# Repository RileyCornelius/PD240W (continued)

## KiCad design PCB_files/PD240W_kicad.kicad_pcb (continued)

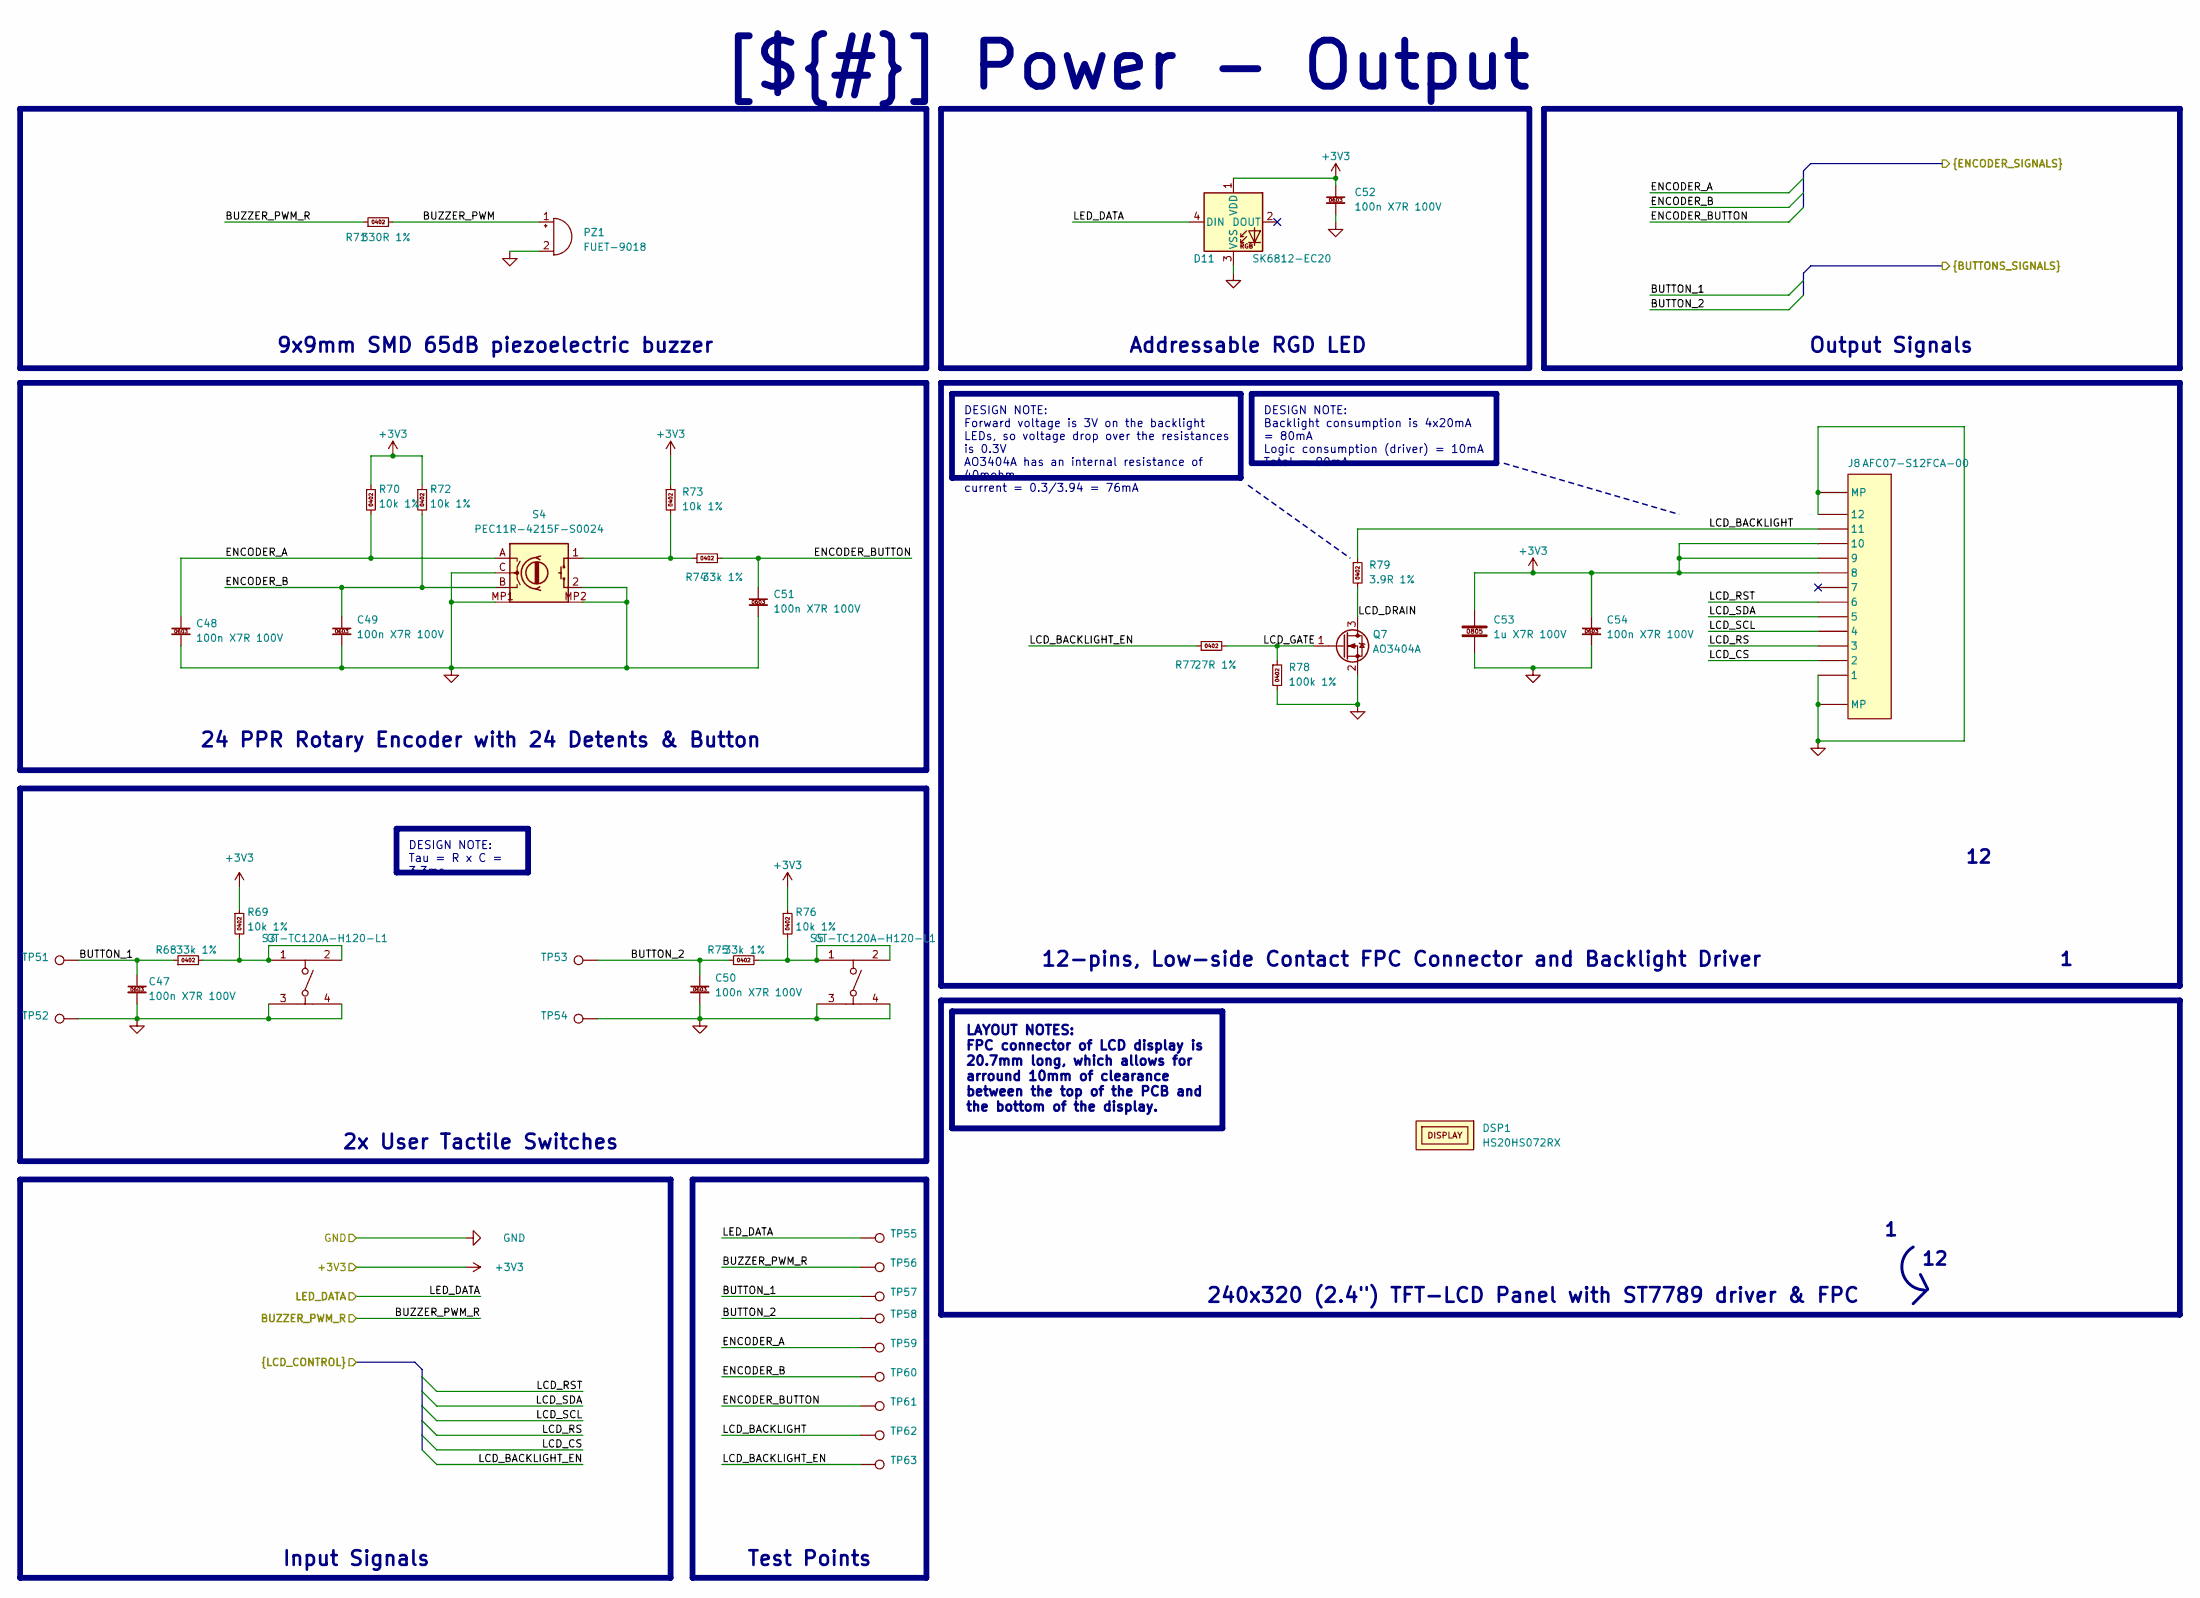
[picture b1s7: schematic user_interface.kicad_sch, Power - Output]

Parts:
C47, C48, C49, C50, C51, C52, C54: 100n X7R 100V; capc_1608_09_l; MFR Part # CL10B104KC8NNNC; LCSC C15725
C53: 1u X7R 100V; capc_2012_14_n; MFR Part # CC0805KKX7R0BB105; LCSC C5370002
D11: SK6812-EC20; MFR Part # SK6812-EC20; LCSC C2909058
DSP1: HS20HS072RX; generic_display_518x362x2_10mm_standoff; MFR Part # HS20HS072RX; LCSC C5329582
J8: AFC07-S12FCA-00; MFR Part # AFC07-S12FCA-00; LCSC C262559
PZ1: FUET-9018; buzzer_9x9x2.1mm; MFR Part # FUET-9018; LCSC C391035
Q7: AO3404A; sot-23-3L_103p_300x130x110_n; MFR Part # AO3404A; LCSC C30010
R68, R74, R75: 33k 1%; resc_1005_04_n; MFR Part # RC0402FR-0733KL; LCSC C138003
R69, R70, R72, R73, R76: 10k 1%; resc_1005_04_n; MFR Part # 0402WGF1002TCE; LCSC C25744
R71: 330R 1%; resc_1005_04_m; MFR Part # 0402WGF3300TCE; LCSC C25104
R77: 27R 1%; resc_1005_04_m; MFR Part # RC0402FR-0727RL; LCSC C138021
R78: 100k 1%; resc_1005_04_m; MFR Part # 0402WGF1003TCE; LCSC C25741
R79: 3.9R 1%; resc_1005_04_m; MFR Part # FRC0402F3R90TS; LCSC C2933095
S3, S5: GT-TC120A-H120-L1; MFR Part # GT-TC120A-H120-L1; LCSC C2762973
S4: PEC11R-4215F-S0024; MFR Part # PEC11R-4215F-S0024; LCSC C143790
TP51, TP52, TP53, TP54: sp_oval_300x100
TP55, TP56, TP57, TP58, TP59, TP60, TP61, TP62, TP63: tp_round_70

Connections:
+3V3: C52.1, C53.1, C54.1, D11.1 (VDD), J8.8, J8.9, J8.10, R69.1, R70.1, R72.1, R73.1, R76.1; also elsewhere on the board
/Project Architecture/MCU - Unit/BUTTON_1: C47.1, R68.1, TP51.1 (1_1), TP57.1 (1_1); also elsewhere on the board
/Project Architecture/MCU - Unit/BUTTON_2: C50.1, R75.1, TP53.1 (1_1), TP58.1 (1_1); also elsewhere on the board
/Project Architecture/MCU - Unit/BUZZER_PWM_R: R71.1, TP56.1 (1_1); also elsewhere on the board
/Project Architecture/MCU - Unit/ENCODER_A: C48.1, R70.2, S4.A, TP59.1 (1_1); also elsewhere on the board
/Project Architecture/MCU - Unit/ENCODER_B: C49.1, R72.2, S4.B, TP60.1 (1_1); also elsewhere on the board
/Project Architecture/MCU - Unit/ENCODER_BUTTON: C51.1, R74.2, TP61.1 (1_1); also elsewhere on the board
/Project Architecture/MCU - Unit/LCD_BACKLIGHT_EN: R77.1, TP63.1 (1_1); also elsewhere on the board
/Project Architecture/MCU - Unit/LCD_CS: J8.2; also elsewhere on the board
/Project Architecture/MCU - Unit/LCD_RS: J8.3; also elsewhere on the board
/Project Architecture/MCU - Unit/LCD_RST: J8.6; also elsewhere on the board
/Project Architecture/MCU - Unit/LCD_SCL: J8.4; also elsewhere on the board
/Project Architecture/MCU - Unit/LCD_SDA: J8.5; also elsewhere on the board
/Project Architecture/MCU - Unit/LED_DATA: D11.4 (DIN), TP55.1 (1_1); also elsewhere on the board
/Project Architecture/User - Interface/BUZZER_PWM: PZ1.1 (+), R71.2
/Project Architecture/User - Interface/LCD_BACKLIGHT: J8.11, R79.1, TP62.1 (1_1)
/Project Architecture/User - Interface/LCD_DRAIN: Q7.3 (D), R79.2
/Project Architecture/User - Interface/LCD_GATE: Q7.1 (G), R77.2, R78.1
GND: C47.2, C48.2, C49.2, C50.2, C51.2, C52.2, C53.2, C54.2, D11.3 (VSS), J8.1, J8.12, J8.MP1 (MP), J8.MP2 (MP), PZ1.2 (-), Q7.2 (S), R78.2, S3.3, S3.4, S4.2, S4.C, S4.MP1, S4.MP2, S5.3, S5.4, TP52.1 (1_1), TP54.1 (1_1); also elsewhere on the board
unnamed: R68.2, R69.2, S3.1, S3.2
unnamed: R73.2, R74.1, S4.1
unnamed: R75.2, R76.2, S5.1, S5.2

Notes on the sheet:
9x9mm SMD 65dB piezoelectric buzzer
Addressable RGD LED
12-pins, Low-side Contact FPC Connector and Backlight Driver
240x320 (2.4") TFT-LCD Panel with ST7789 driver & FPC
24 PPR Rotary Encoder with 24 Detents & Button
Input Signals
Test Points
Output Signals
2x User Tactile Switches
DESIGN NOTE: Backlight consumption is 4x20mA = 80mA Logic consumption (driver) = 10mA Total = 90mA
DESIGN NOTE: Tau = R x C = 3.3ms
DESIGN NOTE: Forward voltage is 3V on the backlight LEDs, so voltage drop over the resistances is 0.3V AO3404A has an internal resistance of 40mohm. current = 0.3/3.94 = 76mA
LAYOUT NOTES: FPC connector of LCD display is 20.7mm long, which allows for arround 10mm of clearance between the top of the PCB and the bottom of the display.
[${#}] ${TITLE}

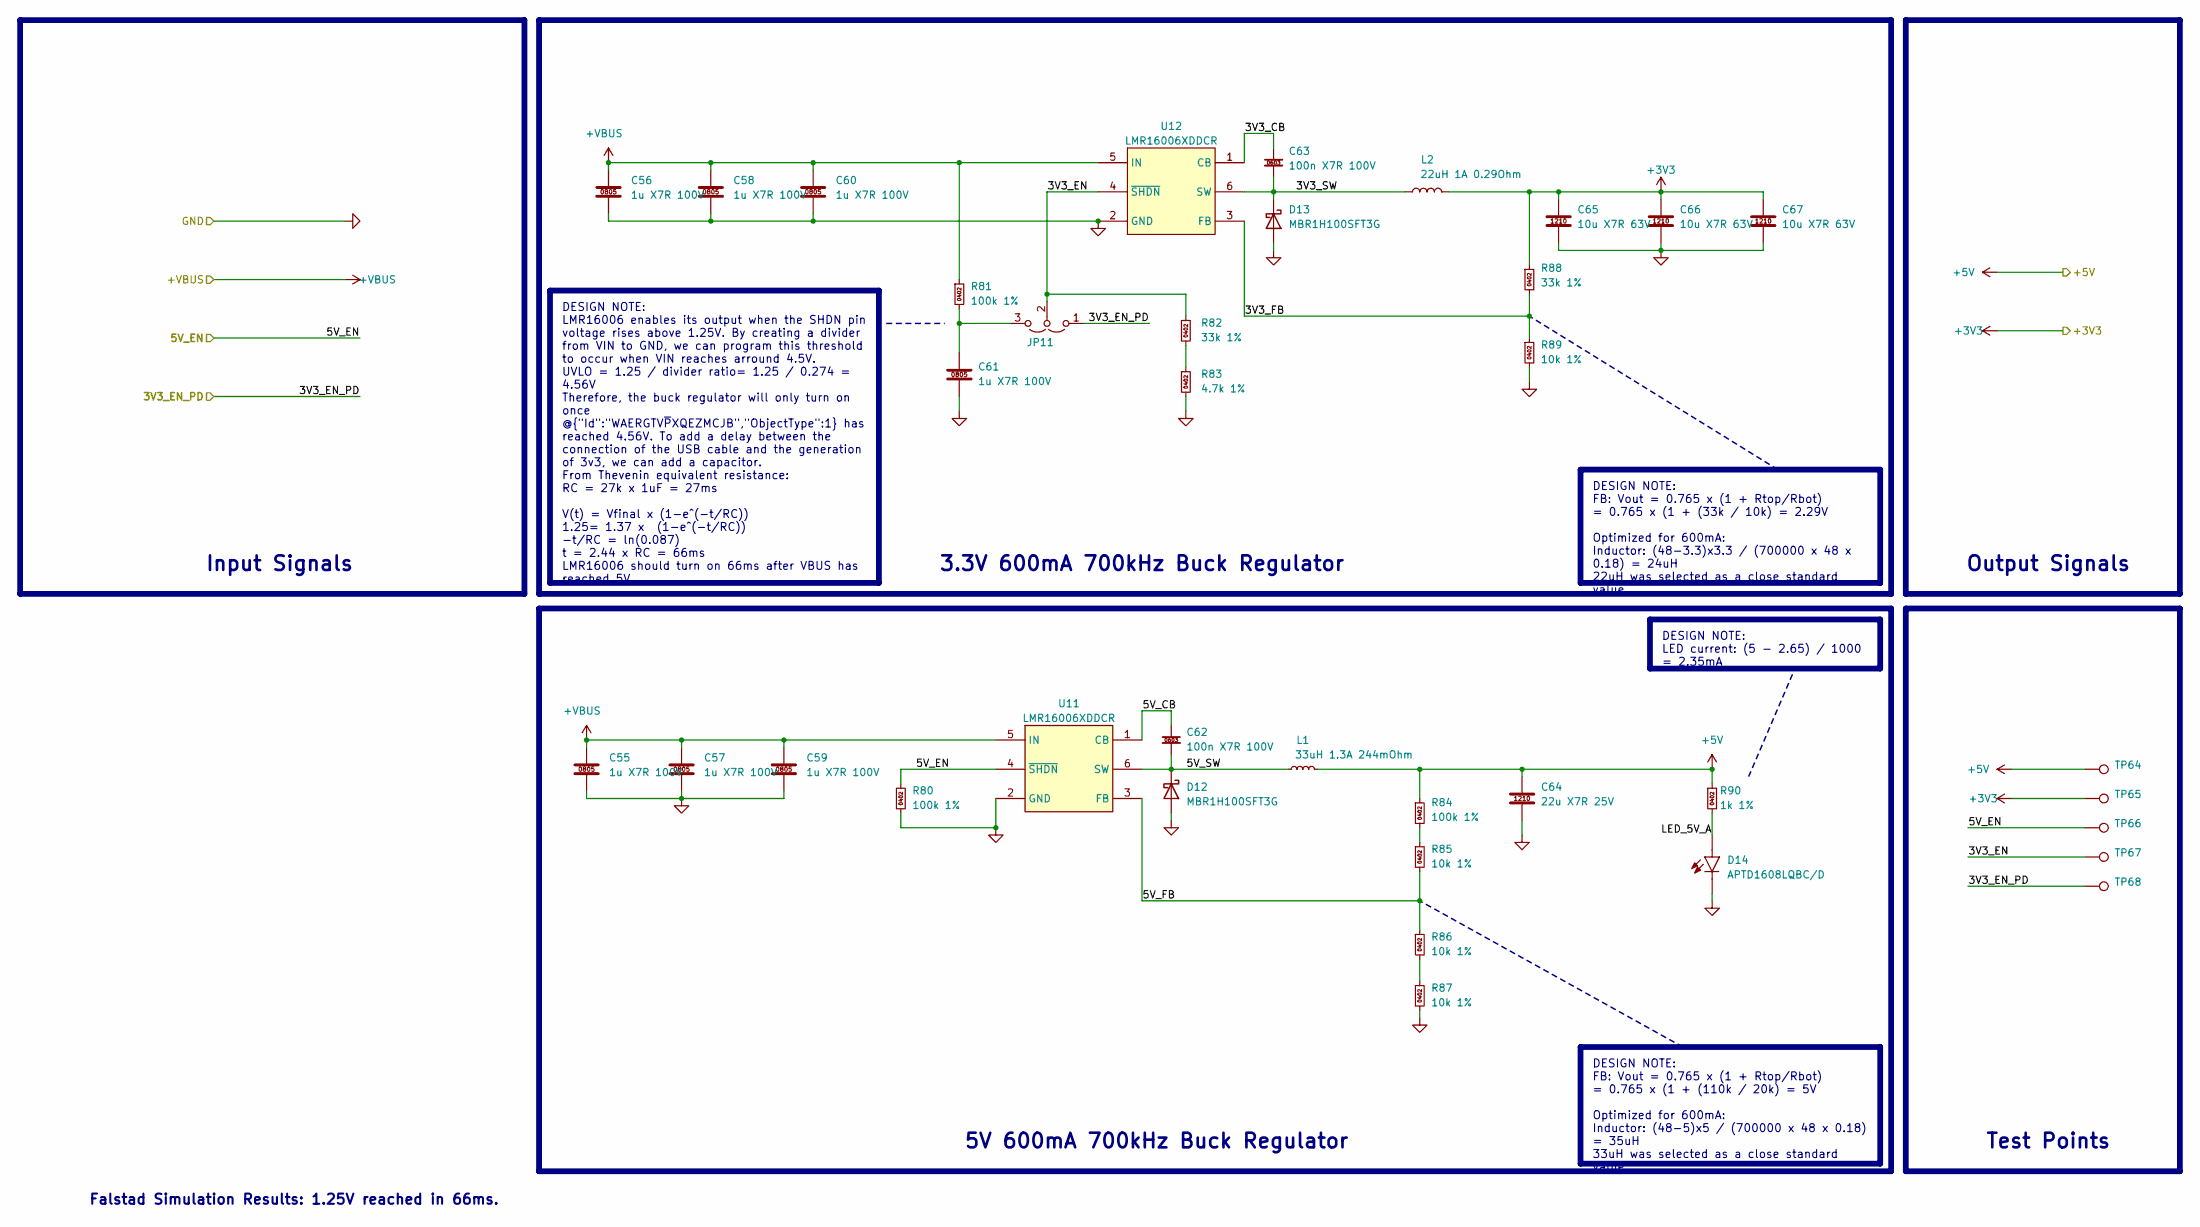
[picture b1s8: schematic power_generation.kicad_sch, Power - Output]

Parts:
C55, C56, C57, C58, C59, C60, C61: 1u X7R 100V; capc_2012_14_n; MFR Part # CC0805KKX7R0BB105; LCSC C5370002
C62, C63: 100n X7R 100V; capc_1608_09_l; MFR Part # CL10B104KC8NNNC; LCSC C15725
C64: 22u X7R 25V; capc_3225_27_n; MFR Part # CL32B226KAJNNNE; LCSC C309062
C65, C66, C67: 10u X7R 63V; capc_3225_27_n; MFR Part # GRM32ER71J106KA12L; LCSC C437568
D12, D13: MBR1H100SFT3G; sod-123fl_305p_260x160x90_n; MFR Part # MBR1H100SFT3G; LCSC C235757
D14: APTD1608LQBC/D; kingbright_0603_blue; MFR Part # APTD1608LQBC/D; LCSC C5344742
JP11: jumper_solder_3pad_no; jumper_solder_3pad_no_40x40_20
L1: 33uH 1.3A 244mOhm; L_APV_ANR5020; MFR Part # SMNR5040-330MT; LCSC C9390
L2: 22uH 1A 0.29Ohm; SWPA4030S220MT; MFR Part # SWPA4030S220MT; LCSC C83472
R80, R81, R84: 100k 1%; resc_1005_04_m; MFR Part # 0402WGF1003TCE; LCSC C25741
R82, R88: 33k 1%; resc_1005_04_n; MFR Part # RC0402FR-0733KL; LCSC C138003
R83: 4.7k 1%; resc_1005_04_m; MFR Part # 0402WGF4701TCE; LCSC C25900
R85, R86, R87, R89: 10k 1%; resc_1005_04_n; MFR Part # 0402WGF1002TCE; LCSC C25744
R90: 1k 1%; resc_1005_04_m; MFR Part # 0402WGF1001TCE; LCSC C11702
TP64, TP65, TP66, TP67, TP68: tp_round_70
U11, U12: LMR16006XDDCR; sot6_p95_290x180x110_n; MFR Part # LMR16006XDDCR; LCSC C87080

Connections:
+3V3: C65.1, C66.1, C67.1, L2.2, R88.1, TP65.1 (1_1); also elsewhere on the board
+5V: C64.1, L1.2, R84.1, R90.1, TP64.1 (1_1); also elsewhere on the board
+VBUS: C55.1, C56.1, C57.1, C58.1, C59.1, C60.1, R81.1, U11.5 (IN), U12.5 (IN); also elsewhere on the board
/Project Architecture/MCU - Unit/5V_EN: R80.1, TP66.1 (1_1), U11.4 (~SHDN); also elsewhere on the board
/Project Architecture/Power - Generation/3V3_CB: C63.1, U12.1 (CB)
/Project Architecture/Power - Generation/3V3_EN: JP11.2 (C), R82.1, TP67.1 (1_1), U12.4 (~SHDN)
/Project Architecture/Power - Generation/3V3_EN_PD: JP11.1 (A), TP68.1 (1_1); also elsewhere on the board
/Project Architecture/Power - Generation/3V3_FB: R88.2, R89.1, U12.3 (FB)
/Project Architecture/Power - Generation/3V3_SW: C63.2, D13.1 (K), L2.1, U12.6 (SW)
/Project Architecture/Power - Generation/5V_CB: C62.1, U11.1 (CB)
/Project Architecture/Power - Generation/5V_FB: R85.2, R86.1, U11.3 (FB)
/Project Architecture/Power - Generation/5V_SW: C62.2, D12.1 (K), L1.1, U11.6 (SW)
/Project Architecture/Power - Generation/LED_5V_A: D14.2 (A), R90.2
GND: C55.2, C56.2, C57.2, C58.2, C59.2, C60.2, C61.2, C64.2, C65.2, C66.2, C67.2, D12.2 (A), D13.2 (A), D14.1 (C), R80.2, R83.2, R87.2, R89.2, U11.2 (GND), U12.2 (GND); also elsewhere on the board
unnamed: C61.1, JP11.3 (B), R81.2
unnamed: R82.2, R83.1
unnamed: R84.2, R85.1
unnamed: R86.2, R87.1

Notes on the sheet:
Input Signals
Output Signals
Test Points
3.3V 600mA 700kHz Buck Regulator
Falstad Simulation Results: 1.25V reached in 66ms.
5V 600mA 700kHz Buck Regulator
DESIGN NOTE: LMR16006 enables its output when the SHDN pin voltage rises above 1.25V. By creating a divider from VIN to GND, we can program this threshold to occur when VIN reaches arround 4.5V. UVLO = 1.25 / divider ratio= 1.25 / 0.274 = 4.56V Therefore, the buck regulator will only turn on once @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
DESIGN NOTE: FB: Vout = 0.765 x (1 + Rtop/Rbot) = 0.765 x (1 + (33k / 10k) = 2.29V Optimized for 600mA: Inductor: (48-3.3)x3.3 / (700000 x 48 x 0.18) = 24uH 22uH was selected as a close standard value.
DESIGN NOTE: LED current: (5 - 2.65) / 1000 = 2.35mA
DESIGN NOTE: FB: Vout = 0.765 x (1 + Rtop/Rbot) = 0.765 x (1 + (110k / 20k) = 5V Optimized for 600mA: Inductor: (48-5)x5 / (700000 x 48 x 0.18) = 35uH 33uH was selected as a close standard value.

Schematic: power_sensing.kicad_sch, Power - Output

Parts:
C23, C24, C25, C26, C27: 100n X7R 100V; capc_1608_09_l; MFR Part # CL10B104KC8NNNC; LCSC C15725
NT1: nt_2pad_20x20_20_60x20; NetTie-2_SMD_Pad0.5mm
R22, R23, R25: 100k 1%; resc_1005_04_m; MFR Part # 0402WGF1003TCE; LCSC C25741
R24: 10k 1%; resc_1005_04_n; MFR Part # 0402WGF1002TCE; LCSC C25744
R26, R32: 4.7k 1%; resc_1005_04_m; MFR Part # 0402WGF4701TCE; LCSC C25900
R27: 10k @25°C; resc_1005_04_m; MFR Part # SDNT1005X103F3950FTF; LCSC C95939
R28, R30, R31: 27R 1%; resc_1005_04_m; MFR Part # RC0402FR-0727RL; LCSC C138021
R29: 8m 1%; WSLP1206_n_current_sense_6m_to_50m; MFR Part # HoLLR1206-1W-8mR-1%; LCSC C2988654
TP27, TP28, TP29, TP30: tp_round_70
U7: INA228AIDGSR; vssop10_50p_300x300x110_mfg; MFR Part # INA228AIDGSR; LCSC C2887910
U8: SN74LVC1G17DBVR; sot25_95p_300x280x145_jedec_mo-178-aa_n; MFR Part # SN74LVC1G17DBVR; LCSC C7836

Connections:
+3V3: C26.1, C27.1, R26.1, U7.6 (VS), U8.5 (VCC); also elsewhere on the board
+VBUS: R22.1, R25.1; also elsewhere on the board
+VBUS_OUT: R29.2, R30.1, TP30.1 (1_1), U7.8 (VBUS); also elsewhere on the board
+VBUS_SENSED: R28.1, R29.1; also elsewhere on the board
/Project Architecture/MCU - Unit/I2C0_SCL: U7.5 (SCL); also elsewhere on the board
/Project Architecture/MCU - Unit/I2C0_SDA: U7.4 (SDA); also elsewhere on the board
/Project Architecture/MCU - Unit/SW_EN_READ: R32.2, TP29.1 (1_1); also elsewhere on the board
/Project Architecture/MCU - Unit/TEMP_SENSE: C24.1, R26.2, R27.1; also elsewhere on the board
/Project Architecture/MCU - Unit/V_SENSE: C23.1, R23.2, R24.1, TP27.1 (1_1); also elsewhere on the board
/Project Architecture/Power - PD Controller/SWITCH_EN: R31.2, TP28.1 (1_1), U8.2 (A); also elsewhere on the board
/Project Architecture/Power - Sensing/INA_ALERT: R31.1, U7.3 (ALERT)
/Project Architecture/Power - Sensing/SENSE_N: C25.2, R30.2, U7.9 (IN-)
/Project Architecture/Power - Sensing/SENSE_P: C25.1, R28.2, U7.10 (IN+)
GND: C23.2, C24.2, C26.2, C27.2, NT1.2, R24.2, U7.1 (A1), U7.2 (A0), U7.7 (GND), U8.3 (GND); also elsewhere on the board
unnamed: NT1.1, R27.2
unnamed: R22.2, R23.1, R25.2
unnamed: R32.1, U8.4 (Y)

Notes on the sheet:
Test Points
Input Signals
85-V, 20-Bit, Ultra-Precise Power/Energy/Charge Monitor With I²C Interface
Temperature Sensing
Output Signals
Input Voltage Sensing
DESIGN NOTE: B-Constant is 3950K 1.2k @ 80°C -> 0.67V 2.5k @ 60°C -> 1.14V 10k @ 25°C -> 2.24V 13k @ 20°C -> 2.42V
DESIGN NOTE: I2C pullups are on Power - PD Conroller schematic
DEBUG NOTE: INA228AIDGSR address when A1 & A0 are tied to GND is 0x40 (7 bits 1000000) (see page 19)
DESIGN NOTE: ADCRANGE = 1 (+- 40.96 mV range) V_{SENSE} = 5A x 0.008 = 40 mV. This utilizes 97.6% of the ADC range, providing the highest possible resolution. Power Dissipation: P = 5² x 0.008 = 0.2W
LAYOUT NOTES: NTC must be placed close and thermally coupled to the ground plane near the relevant heat source. Route away from noisy traces.
LAYOUT NOTES: Place capacitor close to MCU DC pin. Route away from noisy traces.
[${#}] ${TITLE}
DEBUG NOTE: Low side measurement is used to improve thermal coupling, which invert the maths in software.
DESIGN NOTE: Network ratio = 1/16 = 0.0625 @48V V_SENSE = 3V @5V V_SENSE = 0.31V
DEBUG NOTE: ALERT is open-drain and can be configured to latch or not latch the overcurrent event.
DESIGN NOTE: SN74LVC1G17 is a safety buffer to prevent software mistakes. Driving SWEN_READ cannot activate the power switch.

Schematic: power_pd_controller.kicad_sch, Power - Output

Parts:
C9, C12, C14, C15: 10u X7R 63V; capc_3225_27_n; MFR Part # GRM32ER71J106KA12L; LCSC C437568
C10, C16, C20, C21: 100n X7R 100V; capc_1608_09_l; MFR Part # CL10B104KC8NNNC; LCSC C15725
C11, C13: 220p X7R 50V; capc_1005_06_l; MFR Part # CL05B221KB5NNNC; LCSC C296710
C17, C18, C19: 3.3u X5R 25V; capc_1608_09_n; MFR Part # TCC0603X5R335M250CT; LCSC C5360803
C22: 2.2u X7R 100V; capc_2012_14_m; MFR Part # HHV0805R7225K101NSLJ; LCSC C22367838
D5: D3V3F4U6S-7; sot363_sc88_65p_200x125x110_n; MFR Part # D3V3F4U6S-7; LCSC C1869321
D6: B0520LW-7-F; sod-123_270x155135_n; MFR Part # B0520LW-7-F; LCSC C155367
D7: APTD1608LQBC/D; kingbright_0603_blue; MFR Part # APTD1608LQBC/D; LCSC C5344742
J2: 61300411121; we_61300411121; MFR Part # 61300411121; LCSC C5184785; not fitted
JP3, JP4, JP5, JP6, JP7, JP8: jumper_solder_2pad_no; jumper_solder_2pad_no_40x40_20
JP9: jumper_solder_2pad_no_kicad; SolderJumper-2_P1.3mm_Open_RoundedPad1.0x1.5mm
JP10: jumper_solder_3pad_12nc_kicad; SolderJumper-3_P1.3mm_Bridged2Bar12_RoundedPad1.0x1.5mm
Q3, Q4, Q6: AO3404A; sot-23-3L_103p_300x130x110_n; MFR Part # AO3404A; LCSC C30010
Q5: SQJB90EP-T1_GE3; PowerPAKSO-8_127p_513x615x120_n; MFR Part # SQJB90EP-T1_GE3; LCSC C727731
R7, R8, R10, R11, R17: 4.7k 1%; resc_1005_04_m; MFR Part # 0402WGF4701TCE; LCSC C25900
R9, R12, R16: 10k 1%; resc_1005_04_n; MFR Part # 0402WGF1002TCE; LCSC C25744
R13, R14, R15, R19, R20: 100k 1%; resc_1005_04_m; MFR Part # 0402WGF1003TCE; LCSC C25741
R18: 27R 1%; resc_1005_04_m; MFR Part # RC0402FR-0727RL; LCSC C138021
R21: 330R 1%; resc_1005_04_m; MFR Part # 0402WGF3300TCE; LCSC C25104
TP14, TP15, TP16, TP17, TP18, TP19, TP20, TP21, TP22, TP23, TP24, TP25, TP26: tp_round_70
U2: TPS26750SRSMR; qfn32_40p_400x400x100_tp_280x280_mfg; MFR Part # TPS26750SRSMR; LCSC C42166327
U3: CAT24C512YI-GT3; JEDEC_MO-153_AA; MFR Part # CAT24C512YI-GT3; LCSC C56096
U4: LM2765; sot236_p95_290x160x110_n; MFR Part # LM2765M6X/NOPB; LCSC C140270
U5: 74LVC1G08SE-7; sot353_65p_200x125x110_mo-203-aa_n; MFR Part # 74LVC1G08SE-7; LCSC C460522
U6: LTC7004x; msop_10p_300x490x110_tp168x188_n; MFR Part # LTC7004EMSE#PBF; LCSC C690105

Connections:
+1V5_LDO: C9.1, TP23.1 (1_1), U2.2 (ADCIN1), U2.3 (ADCIN2), U2.4 (LDO_1V5)
+3V3: C14.1, D5.5, D7.2 (A), U2.32 (VIN_3V3); also elsewhere on the board
+3V3_EEPROM: C16.1, J2.1, JP9.1 (A), U3.8 (VCC)
+3V3_LDO: C12.1, C17.1, C21.1, D6.2 (A), JP9.2 (B), R7.1, R8.1, R9.1, R10.1, R11.1, R12.1, R14.1, R15.1, TP24.1 (1_1), U2.1 (LDO_3V3), U4.1 (IN), U5.5 (VCC); also elsewhere on the board
+6V6_LDO: C19.1, D6.1 (K), TP25.1 (1_1), U4.5 (OUT), U6.1 (VCC)
+VBUS: JP10.3 (B), Q5.5 (D); also elsewhere on the board
+VBUS_LV: C10.1, U2.26 (VBUS), U2.27 (VBUS); also elsewhere on the board
+VBUS_SENSED: Q5.6 (D), TP22.1 (1_1); also elsewhere on the board
/Project Architecture/MCU - Unit/GPIO14_R: JP8.2 (B); also elsewhere on the board
/Project Architecture/MCU - Unit/GPIO15_R: JP7.2 (B); also elsewhere on the board
/Project Architecture/MCU - Unit/I2C0_SCL: R8.2, U2.9 (I2CT_SCL); also elsewhere on the board
/Project Architecture/MCU - Unit/I2C0_SDA: R7.2, U2.8 (I2CT_SDA); also elsewhere on the board
/Project Architecture/MCU - Unit/PD_GPIO1: TP20.1 (1_1), U2.6 (GPIO1); also elsewhere on the board
/Project Architecture/MCU - Unit/PD_GPIO3: TP21.1 (1_1), U2.18 (GPIO3); also elsewhere on the board
/Project Architecture/MCU - Unit/SWITCH_EN_MANUAL: R13.1, U5.2 (B); also elsewhere on the board
/Project Architecture/MCU - Unit/USB_PD_IRQ: R9.2, TP26.1 (1_1), U2.10 (*I2CT_IRQ); also elsewhere on the board
/Project Architecture/Power - Generation/3V3_EN_PD: U2.31 (GPIO6); also elsewhere on the board
/Project Architecture/Power - PD Controller/CAP+: C18.1, U4.6 (CAP+)
/Project Architecture/Power - PD Controller/CAP-: C18.2, U4.3 (CAP-)
/Project Architecture/Power - PD Controller/CC1: C13.1, U2.24 (CC1); also elsewhere on the board
/Project Architecture/Power - PD Controller/CC2: C11.1, U2.25 (CC2); also elsewhere on the board
/Project Architecture/Power - PD Controller/EPR_EN: U2.7 (GPIO2); also elsewhere on the board
/Project Architecture/Power - PD Controller/I2CC_IRQ: R12.2, U2.17 (*I2CC_IRQ)
/Project Architecture/Power - PD Controller/I2CC_SCL: JP6.2 (B), U2.16 (I2CC_SCL)
/Project Architecture/Power - PD Controller/I2CC_SCL_EEPROM: JP4.2 (B), JP6.1 (A), JP7.1 (A), R11.2, U3.6 (SCL)
/Project Architecture/Power - PD Controller/I2CC_SCL_EXT: D5.1, J2.2, JP4.1 (A)
/Project Architecture/Power - PD Controller/I2CC_SDA: JP5.2 (B), U2.15 (I2CC_SDA)
/Project Architecture/Power - PD Controller/I2CC_SDA_EEPROM: JP3.2 (B), JP5.1 (A), JP8.1 (A), R10.2, U3.5 (SDA)
/Project Architecture/Power - PD Controller/I2CC_SDA_EXT: D5.6, J2.3, JP3.1 (A)
/Project Architecture/Power - PD Controller/LTC_BST: C22.2, U6.9 (BST)
/Project Architecture/Power - PD Controller/LTC_GATE: Q5.2 (G), Q5.4 (G), R18.2, R19.2, R20.2, TP19.1 (1_1), U6.6 (TGDN)
/Project Architecture/Power - PD Controller/POWER_PATH_EN: Q3.1 (G), TP14.1 (1_1), U2.20 (POWER_PATH_EN)
/Project Architecture/Power - PD Controller/PP5V: C15.1, U2.28 (PP5V), U2.29 (PP5V)
/Project Architecture/Power - PD Controller/PP_EN1: Q3.3 (D), Q4.1 (G), R14.2, TP15.1 (1_1)
/Project Architecture/Power - PD Controller/PP_EN2: Q4.3 (D), R15.2, TP16.1 (1_1), U5.1 (A)
/Project Architecture/Power - PD Controller/PP_EN3: R16.1, R17.1, TP17.1 (1_1), U5.4 (Y)
/Project Architecture/Power - PD Controller/SWITCH_EN: Q6.1 (G), R17.2, U6.4 (INP); also elsewhere on the board
/Project Architecture/Power - PD Controller/TS: C22.1, JP10.1 (A), JP10.2 (C), Q5.1 (S), Q5.3 (S), TP18.1 (1_1), U6.8 (TS)
/Project Architecture/Power - PD Controller/~FLT: U2.5 (GPIO0); also elsewhere on the board
GND: C9.2, C10.2, C11.2, C12.2, C13.2, C14.2, C15.2, C16.2, C17.2, C19.2, C20.2, C21.2, D5.2, J2.4, Q3.2 (S), Q4.2 (S), Q6.2 (S), R13.2, R16.2, U2.11 (GND), U2.12 (GND), U2.13 (GPIO11), U2.14 (GND), U2.19 (GND), U2.22 (GPIO4/USB_P/LD1), U2.23 (GPIO5/USB_N/LD2), U2.30 (GPIO7), U2.33 (GND), U3.1 (A0), U3.2 (A1), U3.3 (A2), U3.4 (VSS), U3.7 (WP), U4.2 (GND), U4.4 (SD), U5.3 (GND), U6.2 (VCCUV), U6.3 (GND), U6.5 (OVLO), U6.11 (GND); also elsewhere on the board
unnamed: C20.1, R18.1
unnamed: D7.1 (C), R21.1
unnamed: Q6.3 (D), R21.2
unnamed: R19.1, R20.1, U6.7 (TGUP)

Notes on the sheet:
I²C0
512 Kb I2C CMOS Serial EEPROM
USB Type-C® and USB PD Controller With Integrated Power Switches
Output Signals
Test Points
Input Signals
I²C1
DEBUG NOTE: ADCIN both conected to LDO1.5V result in ADCINx decoded value 5, which activate AlwaysEnableSink mode and I²C address 0x21 (7 bits). (see page 34)
DEBUG NOTE: EEPROM Address: Must be 0x50 (7-bit) on the I2Cc bus for the TPS26750 to find it automatically. (1010000)
DEBUG NOTE: If the gate driver is not working as expected, connect the bootstrap capacitor to +VBUS instead of TS.
LAYOUT NOTE: CC1/CC2 capacitors need to be placed as close as possible to their respective pins and on the same layer as the TPS26750 device.
DESIGN NOTE: 3V3 LDO total current needs to be lower than 5mA at startup: EEPROM read: 1mA POWER OK LED: 0.65mA TPD4S480: 0.16mA LM2765: 0.13mA LTC7004: 0.05mA I²C pull-ups: ~~0.5mA ADC resistors: 0.02mA AND gate: <0.01mA Total ~~2.5mA < 5mA
DESIGN NOTE: The default state for a USB-C port (before or during negotiation, or if negotiation fails) is effectively USB 2.0 specs: 5V @ 500mA. Therefore we want to limit the inrush current. Synapticon drives have an averager of 150uF of input capacitance. As explained in application informations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
DESIGN NOTE: LED current: (3.3 - 2.65)/330 = 2mA
DEBUG NOTE: When flashing the binary configuration to the EEPROM leave the jumper open, and power the EEPROM from an external supply, to avoid I²C bus conflict with TPS26750.
[${#}] ${TITLE}

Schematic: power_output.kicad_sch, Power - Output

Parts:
C28, C29: 10u X7R 63V; capc_3225_27_n; MFR Part # GRM32ER71J106KA12L; LCSC C437568
C30: 100n X7R 100V; capc_1608_09_l; MFR Part # CL10B104KC8NNNC; LCSC C15725
D8: SMAJ48A; do-214ac_440p_430x250x230_n_p; MFR Part # SMAJ48A; LCSC C41376401
F1, F2: FSMD020-1206-R; ptc_1206_08_n; MFR Part # FSMD020-1206-R; LCSC C220145
J3: 24.245.1; fcr7350r; MFR Part # 24.245.1; LCSC C7437326
J4: 24.245.2; fcr7350b; MFR Part # 24.245.2; LCSC C7437327
J5, J6: 1935776; phoenix_1935776; MFR Part # 1935776; LCSC C3817389
R33, R34: 33k 1%; resc_1005_04_n; MFR Part # RC0402FR-0733KL; LCSC C138003
TP31, TP32: 5001; MFR Part # 5001; LCSC C238122; not fitted

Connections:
+3V3: F1.1; also elsewhere on the board
+5V: F2.1; also elsewhere on the board
+VBUS_OUT: C28.1, C29.1, C30.1, D8.1 (A1), J3.1, R33.1, TP31.1 (1_1); also elsewhere on the board
/Project Architecture/Power - Output/3V3_FUSED: F1.2, J6.1
/Project Architecture/Power - Output/5V_FUSED: F2.2, J5.1
GND: C28.2, C29.2, C30.2, D8.2 (A2), J3.MP1 (MP), J3.MP2 (MP), J3.MP3 (MP), J3.MP4 (MP), J4.1, J4.MP1 (MP), J4.MP2 (MP), J4.MP3 (MP), J4.MP4 (MP), J5.2, J6.2, R34.2, TP32.1 (1_1); also elsewhere on the board
unnamed: R33.2, R34.1

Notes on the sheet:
Screw Terminals for 5V
4mm Banana SMT RED & BLACK Output Connectors
Input Signals
DESIGN NOTE: V_r : 48V V_brmin : 53.3V V_c = 77.4V This diode is our best option for 48V, but it won't be enough as TPD4S480 has a 63V maximum input voltage, and LMR16006 65V.
DESIGN NOTE: RC = 66k x 20uF = 1.3ms Safe to touch in 3 seconds max power losses: 0.73mA
[${#}] ${TITLE}
DESIGN NOTE: I_hold = 200mA I_trip = 400mA
FCR7350R - C7437326
LAYOUT NOTES: Space Banana connectors by a standard 19.05mm. Add mechanical stitching vias to +VBUS_OUT and GND to provide mechanical anchors against external torque applied to the connectors.
FCR7350B - C7437327

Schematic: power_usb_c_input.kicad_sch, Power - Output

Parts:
C1, C3, C7: 10n X7R 100V; capc_1005_06_n; MFR Part # CC0402KRX7R0BB103; LCSC C527014
C2: 1u X7R 100V; capc_2012_14_n; MFR Part # CC0805KKX7R0BB105; LCSC C5370002
C4, C6, C8: 100n X7R 100V; capc_1608_09_l; MFR Part # CL10B104KC8NNNC; LCSC C15725
C5: 4.7u; capc_3225_22_n; MFR Part # GCM32DC72A475KE02; LCSC C913445
D1: SMAJ48A; do-214ac_440p_430x250x230_n_p; MFR Part # SMAJ48A; LCSC C41376401
D2, D3: BZT52C18SQ; sod-323_230p_170x125x100_n; MFR Part # BZT52C18SQ; LCSC C2857090
D4: APTD1608LQBC/D; kingbright_0603_blue; MFR Part # APTD1608LQBC/D; LCSC C5344742
FB1: BLM18SN220TH1D; fer_1608_09_n; MFR Part # BLM18SN220TH1D; LCSC C710392
J1: DX07S024JJ2R1300; MFR Part # DX07S024JJ2R1300; LCSC C2977282
JP1: jumper_solder_2pad_no; SolderJumper-2_P1.3mm_Open_RoundedPad1.0x1.5mm
JP2: jumper_solder_2pad_nc_kicad; SolderJumper-2_P1.3mm_Bridged2Bar_RoundedPad1.0x1.5mm
Q1: AGM612AP; vsonp8_65p_330x330x80_mfg; MFR Part # AGM612AP; LCSC C5349119
Q2: AO3404A; sot-23-3L_103p_300x130x110_n; MFR Part # AO3404A; LCSC C30010
R1, R5: 33k 1%; resc_1005_04_n; MFR Part # RC0402FR-0733KL; LCSC C138003
R2: 10k 1%; resc_1005_04_n; MFR Part # 0402WGF1002TCE; LCSC C25744
R3, R4: 100k 1%; resc_1005_04_m; MFR Part # 0402WGF1003TCE; LCSC C25741
R6: 1k 1%; resc_1005_04_m; MFR Part # 0402WGF1001TCE; LCSC C11702
TP1, TP2, TP3, TP4, TP5, TP6, TP7, TP8, TP9, TP12, TP13: tp_round_70
TP10, TP11: sp_oval_300x100
U1: TPD4S480RUKR; wqfn20_40p_300x300x80_tp_170x170_n; MFR Part # TPD4S480RUKR; LCSC C43131250

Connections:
+3V3_LDO: C2.1, D4.2 (A), R2.1, U1.10 (VPWR); also elsewhere on the board
+VBUS: C6.1, FB1.2, Q1.3 (D), TP4.1 (1_1), U1.20 (VBUS); also elsewhere on the board
+VBUS_LV: C8.1, D3.1 (K), Q1.1 (S), R3.1, TP5.1 (1_1), U1.19 (VBUS_LV); also elsewhere on the board
/Project Architecture/MCU - Unit/USB_D_N: U1.14 (SBU2); also elsewhere on the board
/Project Architecture/MCU - Unit/USB_D_P: U1.15 (SBU1); also elsewhere on the board
/Project Architecture/Power - PD Controller/CC1: TP1.1 (1_1), U1.12 (CC1); also elsewhere on the board
/Project Architecture/Power - PD Controller/CC2: TP2.1 (1_1), U1.11 (CC2); also elsewhere on the board
/Project Architecture/Power - PD Controller/EPR_EN: TP7.1 (1_1), U1.16 (EPR_EN); also elsewhere on the board
/Project Architecture/Power - PD Controller/~FLT: R2.2, TP8.1 (1_1), U1.9 (~FLT); also elsewhere on the board
/Project Architecture/Power - USB-C Input/+VBUS_C: C1.1, C3.1, C5.1, D1.1 (A1), FB1.1, J1.A4, J1.A9, J1.B4, J1.B9, TP3.1 (1_1), TP10.1 (1_1)
/Project Architecture/Power - USB-C Input/+VBUS_LV/2: Q2.1 (G), R3.2, R4.1, TP9.1 (1_1)
/Project Architecture/Power - USB-C Input/CC1_C: J1.A5, TP12.1 (1_1), U1.4 (C_CC1), U1.7 (RPD_G1)
/Project Architecture/Power - USB-C Input/CC2_C: J1.B5, TP13.1 (1_1), U1.5 (C_CC2), U1.6 (RPD_G2)
/Project Architecture/Power - USB-C Input/EPR_BLK_G: C7.2, JP1.1 (A), R1.2, TP6.1 (1_1), U1.17 (EPR_BLK_G)
/Project Architecture/Power - USB-C Input/LED_IN_D: Q2.3 (D), R6.2
/Project Architecture/Power - USB-C Input/LED_IN_K: D4.1 (C), R6.1
/Project Architecture/Power - USB-C Input/USB_D_C_N: J1.A7, J1.B7, U1.2 (C_SBU2)
/Project Architecture/Power - USB-C Input/USB_D_C_P: J1.A6, J1.B6, U1.1 (C_SBU1)
/Project Architecture/Power - USB-C Input/VBIAS: C4.1, U1.3 (VBIAS)
/Project Architecture/Power - USB-C Input/VBUS_LV_GATE: C7.1, D2.1 (K), JP1.2 (B), JP2.1 (A), JP2.2 (B), Q1.2 (G), R1.1
GND: C1.2, C2.2, C3.2, C4.2, C5.2, C6.2, C8.2, D1.2 (A2), J1.A1, J1.A12, J1.B1, J1.B12, J1.MP1 (MP), J1.MP2 (MP), J1.MP3 (MP), J1.MP4 (MP), Q2.2 (S), R5.2, TP11.1 (1_1), U1.8 (GND), U1.13 (GND), U1.18 (GND), U1.21 (EP); also elsewhere on the board
unnamed: D2.2 (A), D3.2 (A)
unnamed: R4.2, R5.1

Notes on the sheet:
USB Type-C™ 48V EPR port protector with short-to-VBUS overvoltage and IEC ESD protection
Test Points
Output Signals
Input Signals
USB-C 3.2 Gen2 48V 5A SMD receptacle
DEBUG NOTE: FLT is open-drain and requires a pull-up. To save board space, it could be removed, as TPS26750 has configurable internal pull-ups.
DESIGN NOTE: TPD4S480 have only 4uA of sourcing curent at EPR_BLK_G. BZT52C18SQ have a maximum leakage current of 0.1uA. Worst case sinking current: (21.17V - 17.1) / 33000 = 123 uA Turn-on time = 10nF x 12V / 4uA = 12ms
LAYOUT NOTE: Place the capacitors next to the VBUS pins.
DESIGN NOTE: 22ohm @ 100Mhz 4mohm @ DC 8A rated @ 85°C
[${#}] ${TITLE}
DESIGN NOTE: (3.3 - 2.65)/1000 = 0.65mA During dead-battery boot mode, TPS26750 internal LDO's can only source 5mA, this is why LED current as been reduced.
DESIGN NOTE: V_r : 48V V_brmin : 53.3V V_c = 77.4V This diode is our best option for 48V, but it won't be enough as TPD4S480 has a 63V maximum input voltage, and LMR16006 65V.
DEBUG NOTE: +VBUS_C and GND solder pads to test PCB with external supply at limited current.
DESIGN NOTE: +VBUS_LV/2 = 2.85V @ +VBUS_LV = 5V (min) 14.3V @ +VBUS_LV/2 = 25V (max) Vgs th < +VBUS_LV/2 < Vgs max 2.6V < +VBUS_LV/2 < 20V
DESIGN NOTE: VBUS blocking fet needs to have Vds ≥ 48V (in case TPD fails) and Vgs ≥ 0.42 x 50.4V = 21.16V. Since most FETs in this package have a +- 20V Vgs, zener diodes are used to clamp Vgs to 18V.
DESIGN NOTE: Pin A6 & B6 as well as A7 & B7 need to be connected together, to be able to use he USB-C connector in both directions.
DESIGN NOTE: RPD_G1/2 need to be tied to C_CC1/2 to enable dead battery support, to allow the device to be detected as a source by the USB-C source.
